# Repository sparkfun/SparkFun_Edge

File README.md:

SparkFun Edge 2
========================================

[*SparkFun Edge 2 (DEV-15420)*](https://www.sparkfun.com/products/15420)

Edge computing is here! You've probably heard of this latest entry to the long lineage of tech buzzwords like "IoT," "LoRa," and "cloud" before it, but what is “the edge” and why does it matter? The cloud is impressively powerful but all-the-time connection requires power and connectivity that may not be available. Edge computing handles discrete tasks such as determining if someone said "yes" and responds accordingly. The audio analysis is done at the edge rather than on the web. This dramatically reduces costs and complexity while limiting potential data privacy leaks.

In collaboration with Google and Ambiq, SparkFun's Edge 2 Development Board is based around the newest edge technology and is perfect for getting your feet wet with voice and even gesture recognition without relying on the distant services of other companies. The truly special feature is in the utilization of SparkFun's open-source and FCC Certified Artemis module, whose ultra-efficient ARM Cortex-M4F 48MHz (with 96MHz burst mode) processor, is spec’d to run TensorFlow Lite using only 6uA/MHz. The SparkFun Edge 2 board currently measures ~1.6mA@3V and 48MHz and can run solely on a CR2032 coin cell battery for up to 10 days. Artemis sports all the cutting edge features expected of modern microcontrollers including six configurable I2C/SPI masters, two UARTs, one I2C/SPI slave, a 15-channel 14-bit ADC, and a dedicated Bluetooth processor that supports BLE5. On top of all that the Artemis has 1MB of flash and 384KB of SRAM memory - plenty for the vast majority of applications.

On the Edge 2 you'll have built-in access to sensors, Bluetooth, I2C expansion, and GPIO inputs/outputs. To support edge computing cases like voice recognition the Edge 2 board features two MEMS microphones, an ST LIS2DH12 3-axis accelerometer on its own I2C bus, and a connector to interface to an OV7670 camera (sold separately & functionality coming soon). As TensorFlow updates their algorithms more and more features will open up for the SparkFun Edge 2. An onboard Bluetooth antenna gives the Edge 2 out-of-the-box connectivity. Also available on the board is a Qwiic connector to add I2C sensors/devices, four LEDs, and four GPIO pins. To boast the low-power capabilities of the board we've outfitted it with battery operation from the CR2032 coin cell holder. Programming the board is taken care of with an external USB-serial adapter like the Serial Basic Breakout via a serial bootloader, but for more advanced users we've also made available the JTAG programming and debugger port.

As a brave explorer of this new technology, you'll have to use some advanced concepts but don't worry. Between Ambiq Micro's Software Development Kit and our SDK Setup Guide you'll have access to plenty of examples to begin working with your hardware.

Now get out there and make something amazing with the latest machine learning technology at your very own fingertips!

Repository Contents
-------------------

* **/Documentation** - Data sheets, additional product information
* **/Firmware** - Arduino test firmware sketch
* **/Hardware** - Eagle design files (.brd, .sch)
* **/Production** - Production panel files (.brd)

Documentation
--------------
* **[Board Support Package (BSP)](https://github.com/sparkfun/SparkFun_Edge_BSP)** - Ambiq SDK Board Support Package for the SparkFun Edge.
* **[Edge Board Hookup Guide](https://learn.sparkfun.com/tutorials/sparkfun-edge-hookup-guide)** - Basic hookup guide for the SparkFun Edge.
* **[Software Development Kit (SDK) Setup Guide](https://learn.sparkfun.com/tutorials/using-sparkfun-edge-board-with-ambiq-apollo3-sdk)** - Software Development Kit for working with the SparkFun Edge.

Product Versions
----------------
* [DEV-15420](https://www.sparkfun.com/products/15420)- SparkFun Edge 2 w/ Artemis Module
* [DEV-15170](https://www.sparkfun.com/products/15170)- SparkFun Edge

Version History
---------------
* [v20](https://github.com/sparkfun/SparkFun_Edge/tree/v2.0.0) - Edge with the Artemis
* [v10](https://github.com/sparkfun/SparkFun_Edge/tree/v10) - Initial HW release

License Information
-------------------

This product is _**open source**_! 

Please review the LICENSE.md file for license information. 

If you have any questions or concerns on licensing, please contact techsupport@sparkfun.com.

Distributed as-is; no warranty is given.

- Your friends at SparkFun.

_<COLLABORATION CREDIT>_

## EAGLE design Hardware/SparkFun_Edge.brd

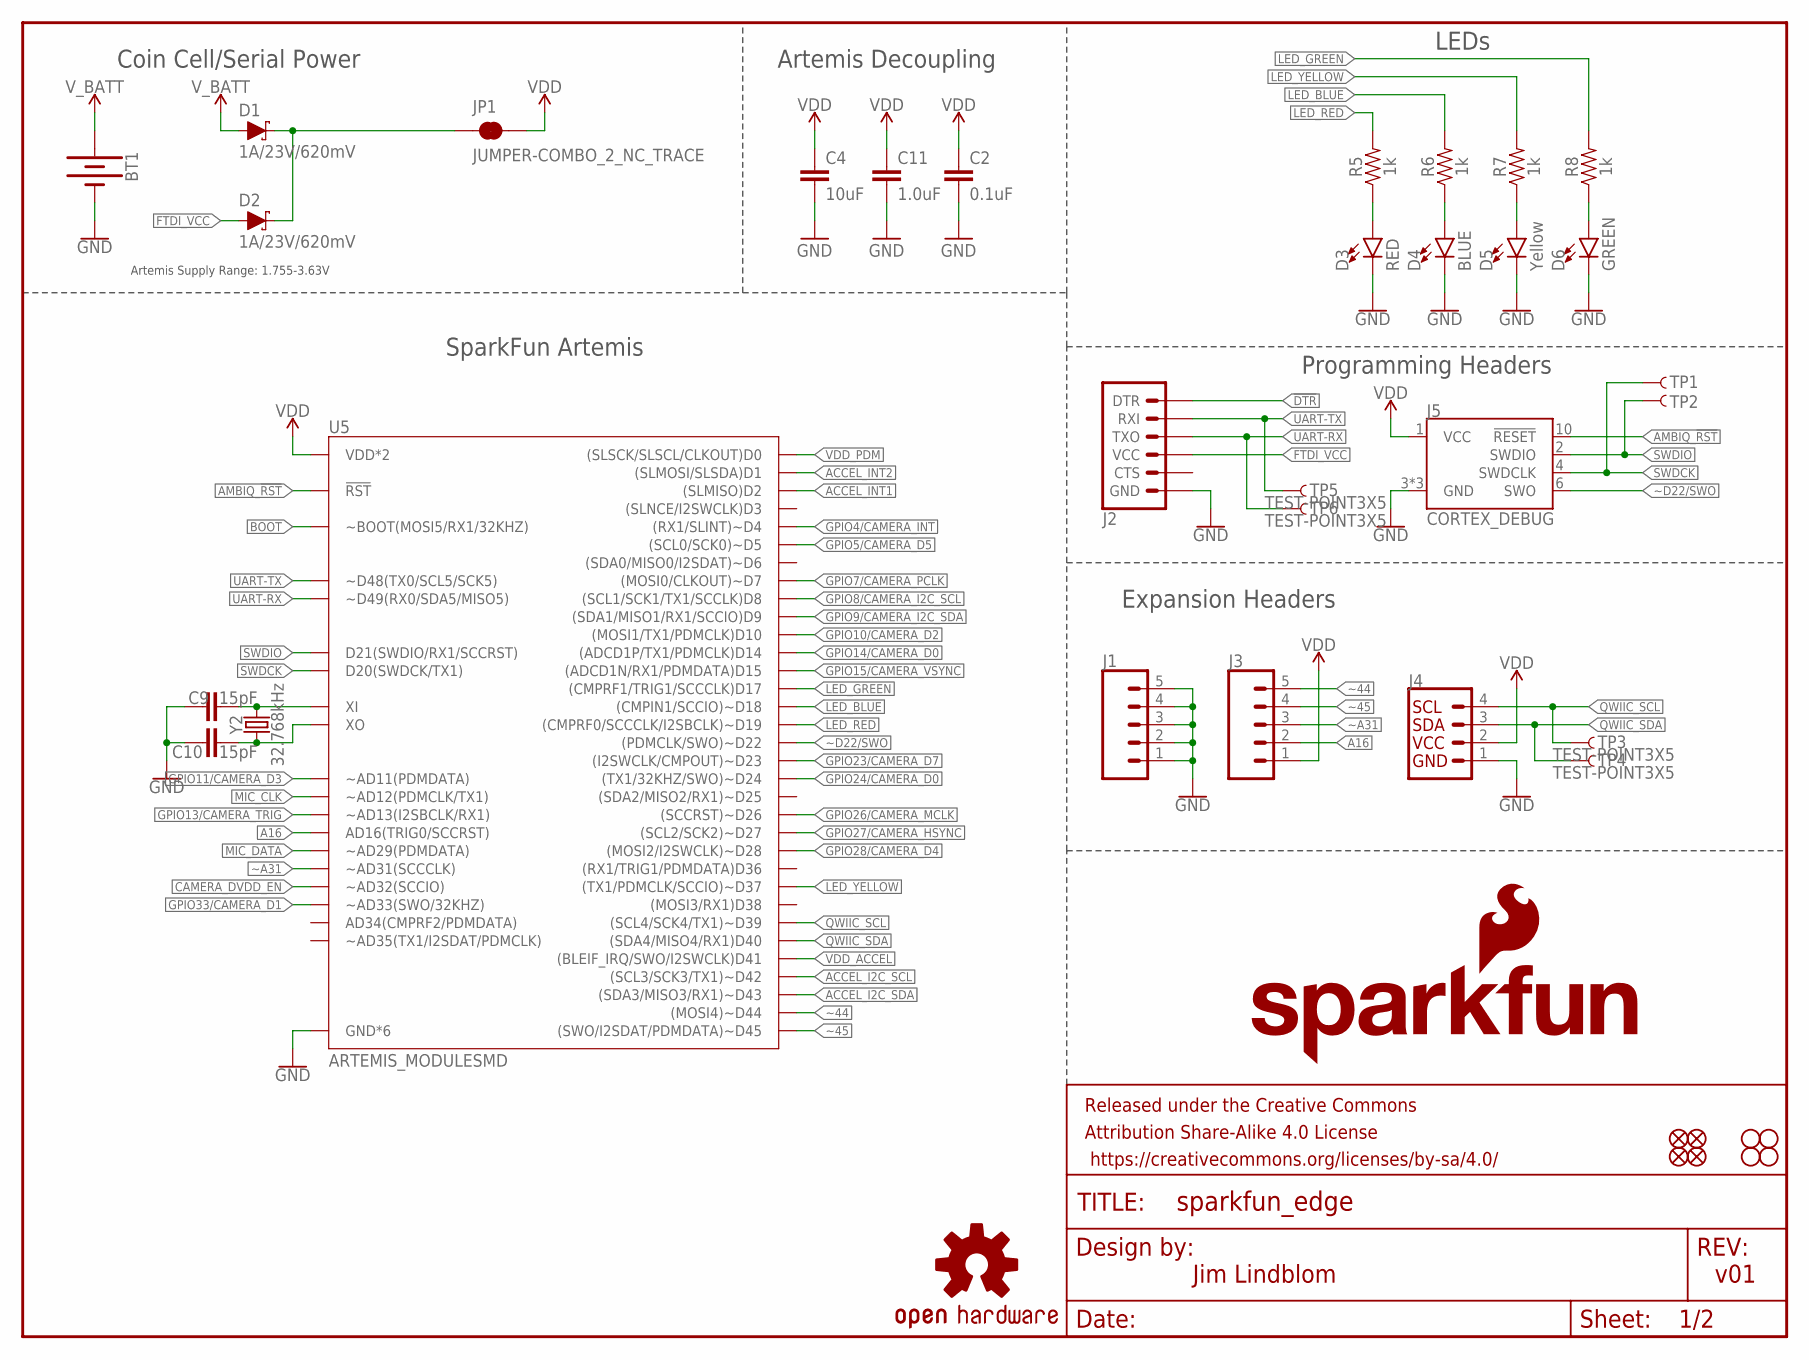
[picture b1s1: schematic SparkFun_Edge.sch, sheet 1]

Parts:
BT1: BATTERY-20MM_SMD_4LEGS_OVERPASTE_INNER; BATTCON_20MM_4LEGS_OVERPASTE_INNER
C2: 0.1uF; 0402-TIGHT
C4: 10uF; 0603
C9, C10: 15pF; 0402-TIGHT
C11: 1.0uF; 0402-TIGHT
D1, D2: 1A/23V/620mV; SOD-323
D3: RED; LED-0603
D4: BLUE; LED-0603
D5: Yellow; LED-0603
D6: GREEN; LED-0603
FD1, FD2, FD3, FD4: FIDUCIAL1X2; FIDUCIAL-1X2
FRAME1: FRAME-LETTER; CREATIVE_COMMONS
H1, H2, H3, H4: STAND-OFF
J1, J3: CONN_05NO_SILK; 1X05_NO_SILK
J2: 6_PIN_SERIAL_TARGETSMD; 1X06-SMD_RA_MALE
J4: QWIIC_CONNECTORJS-1MM; JST04_1MM_RA
J5: CORTEX_DEBUG; 2X5-PTH-1.27MM
JP1: JUMPER-COMBO_2_NC_TRACE; COMBO-JUMPER_2_NC_TRACE
LOGO1: SFE_LOGO_NAME_FLAME.1_INCH; SFE_LOGO_NAME_FLAME_.1
LOGO2: OSHW-LOGOS; OSHW-LOGO-S
R5, R6, R7, R8: 1k; 0603
TP1, TP2, TP3, TP4, TP5, TP6: TEST-POINT3X5; PAD.03X.05
U5: ARTEMIS_MODULESMD; ARTEMIS_FP
Y2: 32.768kHz; CRYSTAL-SMD-3.2X1.5MM

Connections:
!DTR: J2.1 (DTR); also elsewhere on the board
A16: J3.2, U5.AD16 (AD16(TRIG0/SCCRST))
ACCEL_I2C_SCL: U5.~D42 ((SCL3/SCK3/TX1)~D42); also elsewhere on the board
ACCEL_I2C_SDA: U5.~D43 ((SDA3/MISO3/RX1)~D43); also elsewhere on the board
ACCEL_INT1: U5.D2 ((SLMISO)D2); also elsewhere on the board
ACCEL_INT2: U5.D1 ((SLMOSI/SLSDA)D1); also elsewhere on the board
AMBIQ_!RST: J5.10 (!RESET), U5.~RST (!RST); also elsewhere on the board
BOOT: U5.BOOT (~BOOT(MOSI5/RX1/32KHZ)); also elsewhere on the board
CAMERA_DVDD_EN: U5.~AD32 (~AD32(SCCIO)); also elsewhere on the board
FTDI_VCC: D2.A, J2.4 (VCC)
GND: BT1.2 (-), C2.1, C4.2, C9.1, C10.1, C11.2, D3.C, D4.C, D5.C, D6.C, J1.1, J1.2, J1.3, J1.4, J1.5, J2.6 (GND), J4.1, J5.3 (GND), J5.5 (GND), J5.9 (GND), U5.GND@1 (GND*6), U5.GND@22 (GND*6), U5.GND@38 (GND*6), U5.GND@39 (GND*6), U5.GND@47 (GND*6), U5.GND@59 (GND*6); also elsewhere on the board
GPIO4/CAMERA_INT: U5.~D4 ((RX1/SLINT)~D4); also elsewhere on the board
GPIO5/CAMERA_D5: U5.~D5 ((SCL0/SCK0)~D5); also elsewhere on the board
GPIO7/CAMERA_PCLK: U5.D7 ((MOSI0/CLKOUT)~D7); also elsewhere on the board
GPIO8/CAMERA_I2C_SCL: U5.D8 ((SCL1/SCK1/TX1/SCCLK)D8); also elsewhere on the board
GPIO9/CAMERA_I2C_SDA: U5.D9 ((SDA1/MISO1/RX1/SCCIO)D9); also elsewhere on the board
GPIO10/CAMERA_D2: U5.D10 ((MOSI1/TX1/PDMCLK)D10); also elsewhere on the board
GPIO11/CAMERA_D3: U5.~AD11 (~AD11(PDMDATA)); also elsewhere on the board
GPIO13/CAMERA_TRIG: U5.~AD13 (~AD13(I2SBCLK/RX1)); also elsewhere on the board
GPIO14/CAMERA_D0: U5.D14 ((ADCD1P/TX1/PDMCLK)D14); also elsewhere on the board
GPIO15/CAMERA_VSYNC: U5.D15 ((ADCD1N/RX1/PDMDATA)D15); also elsewhere on the board
GPIO23/CAMERA_D7: U5.~D23 ((I2SWCLK/CMPOUT)~D23); also elsewhere on the board
GPIO24/CAMERA_D0: U5.~D24 ((TX1/32KHZ/SWO)~D24); also elsewhere on the board
GPIO26/CAMERA_MCLK: U5.~D26 ((SCCRST)~D26); also elsewhere on the board
GPIO27/CAMERA_HSYNC: U5.~D27 ((SCL2/SCK2)~D27); also elsewhere on the board
GPIO28/CAMERA_D4: U5.~D28 ((MOSI2/I2SWCLK)~D28); also elsewhere on the board
GPIO33/CAMERA_D1: U5.~AD33/SWO (~AD33(SWO/32KHZ)); also elsewhere on the board
LED_BLUE: R6.2, U5.~D18 ((CMPIN1/SCCIO)~D18)
LED_GREEN: R8.2, U5.D17 ((CMPRF1/TRIG1/SCCCLK)D17)
LED_RED: R5.2, U5.~D19 ((CMPRF0/SCCCLK/I2SBCLK)~D19)
LED_YELLOW: R7.2, U5.~D37 ((TX1/PDMCLK/SCCIO)~D37)
MIC_CLK: U5.~AD12 (~AD12(PDMCLK/TX1)); also elsewhere on the board
MIC_DATA: U5.~AD29 (~AD29(PDMDATA)); also elsewhere on the board
unnamed: C9.2, U5.XI, Y2.P$2 (2)
unnamed: D4.A, R6.1
unnamed: D3.A, R5.1
unnamed: D5.A, R7.1
unnamed: D6.A, R8.1
QWIIC_SCL: J4.4, TP3.P$1, U5.~D39 ((SCL4/SCK4/TX1)~D39)
QWIIC_SDA: J4.3, TP4.P$1, U5.D40 ((SDA4/MISO4/RX1)D40)
SWDCK: J5.4 (SWDCLK), TP1.P$1, U5.SWDCK (D20(SWDCK/TX1))
SWDIO: J5.2 (SWDIO), TP2.P$1, U5.SWDIO (D21(SWDIO/RX1/SCCRST))
UART-RX: J2.3 (TXO), TP6.P$1, U5.RXI-0 (~D49(RX0/SDA5/MISO5))
UART-TX: J2.2 (RXI), TP5.P$1, U5.TXO-0 (~D48(TX0/SCL5/SCK5))
VDD: C2.2, C4.1, C11.1, J3.1, J4.2, J5.1 (VCC), JP1.2, JP1.4 (2), U5.VDD@36 (VDD*2), U5.VDD@37 (VDD*2); also elsewhere on the board
VDD_ACCEL: U5.D41 ((BLEIF_IRQ/SWO/I2SWCLK)D41); also elsewhere on the board
VDD_PDM: U5.D0 ((SLSCK/SLSCL/CLKOUT)D0); also elsewhere on the board
VIN1: D1.C, D2.C, JP1.1, JP1.3 (1)
V_BATT: BT1.1 (+), D1.A
X0: C10.2, U5.XO, Y2.P$1 (1)
~44: J3.5, U5.~D44 ((MOSI4)~D44)
~45: J3.4, U5.~D45 ((SWO/I2SDAT/PDMDATA)~D45)
~A31: J3.3, U5.~AD31 (~AD31(SCCCLK))
~D22/SWO: J5.6 (SWO), U5.~D22 ((PDMCLK/SWO)~D22)

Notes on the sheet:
v01
Jim Lindblom
Artemis Supply Range: 1.755-3.63V
SparkFun Artemis
Coin Cell/Serial Power
Artemis Decoupling
LEDs
Programming Headers
Expansion Headers

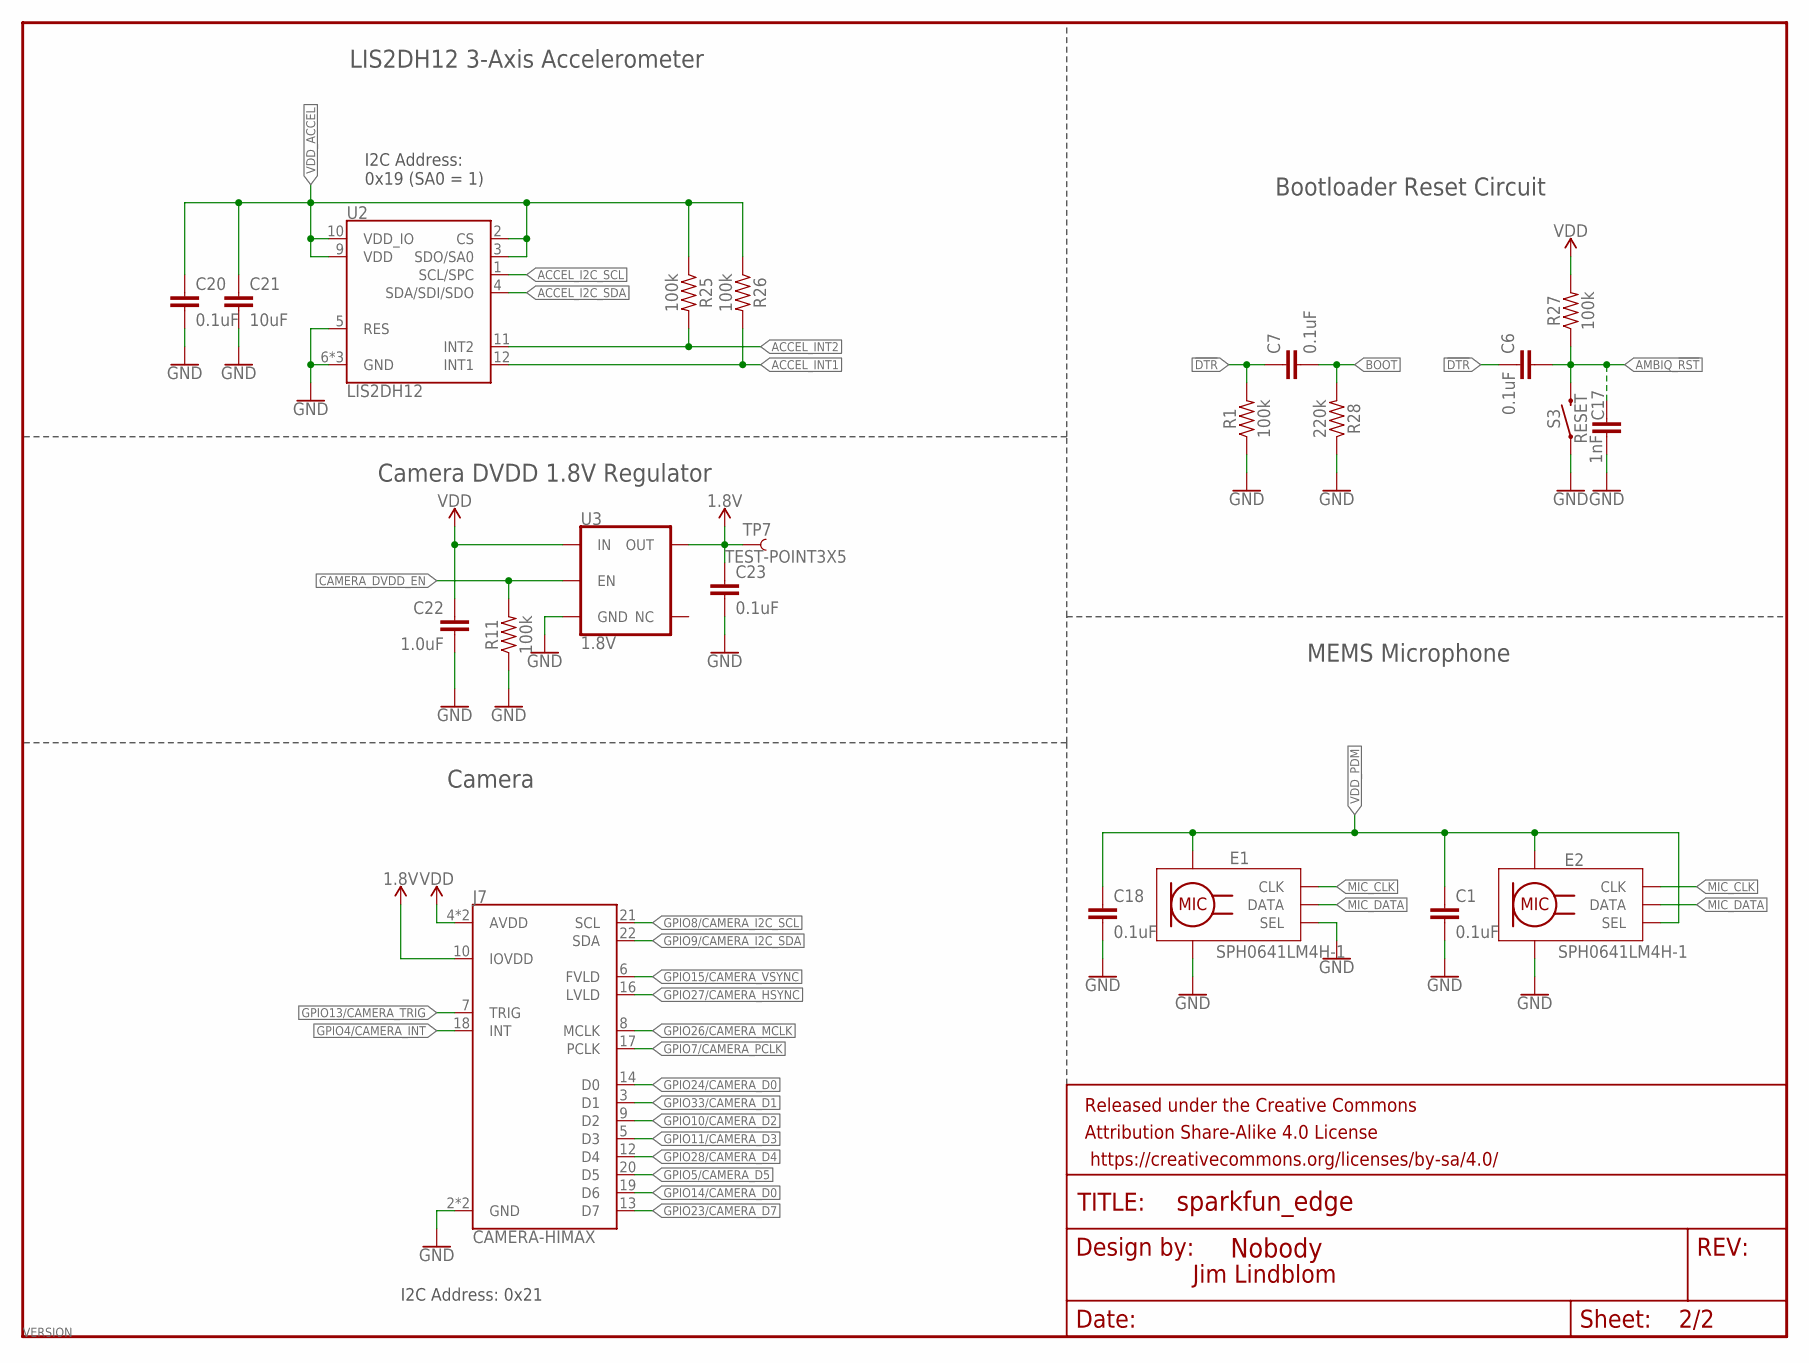
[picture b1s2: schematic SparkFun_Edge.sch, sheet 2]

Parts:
C1, C18, C20, C23: 0.1uF; 0402-TIGHT
C6, C7: 0.1uF; 0603
C17: 1nF; 0603
C21: 10uF; 0603
C22: 1.0uF; 0402-TIGHT
E1, E2: SPH0641LM4H-1; SPH0641LM4H-1_MICROPHONE
FRAME2: FRAME-LETTERNO_PACKAGE; DUMMY
J7: CAMERA-HIMAX; FPC-24-AMPHENOL-SFV24R-1STE1HLF
R1, R27: 100k; 0603
R11, R25, R26: 100k; 0402-TIGHT
R28: 220k; 0603
S3: RESET; TACTILE_SWITCH_SMD_4.6X2.8MM
TP7: TEST-POINT3X5; PAD.03X.05
U2: LIS2DH12; LGA-12-LISDH12
U3: 1.8V; SOT23-5

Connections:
1.8V: C23.1, J7.10 (IOVDD), TP7.P$1, U3.5 (OUT)
!DTR: C6.1, C7.1, R1.2; also elsewhere on the board
ACCEL_I2C_SCL: U2.1 (SCL/SPC); also elsewhere on the board
ACCEL_I2C_SDA: U2.4 (SDA/SDI/SDO); also elsewhere on the board
ACCEL_INT1: R26.2, U2.12 (INT1); also elsewhere on the board
ACCEL_INT2: R25.2, U2.11 (INT2); also elsewhere on the board
AMBIQ_!RST: C6.2, C17.1, R27.1, S3.3 (2), S3.4 (2); also elsewhere on the board
BOOT: C7.2, R28.2; also elsewhere on the board
CAMERA_DVDD_EN: R11.2, U3.3 (EN); also elsewhere on the board
GND: C1.2, C17.2, C18.2, C20.2, C21.2, C22.2, C23.2, E1.2 (SEL), E1.3 (GND), E1.6 (GND), E1.7 (GND), E1.8 (GND), E2.3 (GND), E2.6 (GND), E2.7 (GND), E2.8 (GND), J7.2 (GND), J7.15 (GND), R1.1, R11.1, R28.1, S3.1, S3.2 (1), U2.5 (RES), U2.6 (GND), U2.7 (GND), U2.8 (GND), U3.2 (GND); also elsewhere on the board
GPIO4/CAMERA_INT: J7.18 (INT); also elsewhere on the board
GPIO5/CAMERA_D5: J7.20 (D5); also elsewhere on the board
GPIO7/CAMERA_PCLK: J7.17 (PCLK); also elsewhere on the board
GPIO8/CAMERA_I2C_SCL: J7.21 (SCL); also elsewhere on the board
GPIO9/CAMERA_I2C_SDA: J7.22 (SDA); also elsewhere on the board
GPIO10/CAMERA_D2: J7.9 (D2); also elsewhere on the board
GPIO11/CAMERA_D3: J7.5 (D3); also elsewhere on the board
GPIO13/CAMERA_TRIG: J7.7 (TRIG); also elsewhere on the board
GPIO14/CAMERA_D0: J7.19 (D6); also elsewhere on the board
GPIO15/CAMERA_VSYNC: J7.6 (FVLD); also elsewhere on the board
GPIO23/CAMERA_D7: J7.13 (D7); also elsewhere on the board
GPIO24/CAMERA_D0: J7.14 (D0); also elsewhere on the board
GPIO26/CAMERA_MCLK: J7.8 (MCLK); also elsewhere on the board
GPIO27/CAMERA_HSYNC: J7.16 (LVLD); also elsewhere on the board
GPIO28/CAMERA_D4: J7.12 (D4); also elsewhere on the board
GPIO33/CAMERA_D1: J7.3 (D1); also elsewhere on the board
MIC_CLK: E1.4 (CLK), E2.4 (CLK); also elsewhere on the board
MIC_DATA: E1.1 (DATA), E2.1 (DATA); also elsewhere on the board
VDD: C22.1, J7.4 (AVDD), J7.11 (AVDD), R27.2, U3.1 (IN); also elsewhere on the board
VDD_ACCEL: C20.1, C21.1, R25.1, R26.1, U2.2 (CS), U2.3 (SDO/SA0), U2.9 (VDD), U2.10 (VDD_IO); also elsewhere on the board
VDD_PDM: C1.1, C18.1, E1.5 (VDD), E2.2 (SEL), E2.5 (VDD); also elsewhere on the board

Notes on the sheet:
Camera DVDD 1.8V Regulator
LIS2DH12 3-Axis Accelerometer
Jim Lindblom
I2C Address: 0x19 (SA0 = 1)
I2C Address: 0x21
Camera
MEMS Microphone
Bootloader Reset Circuit

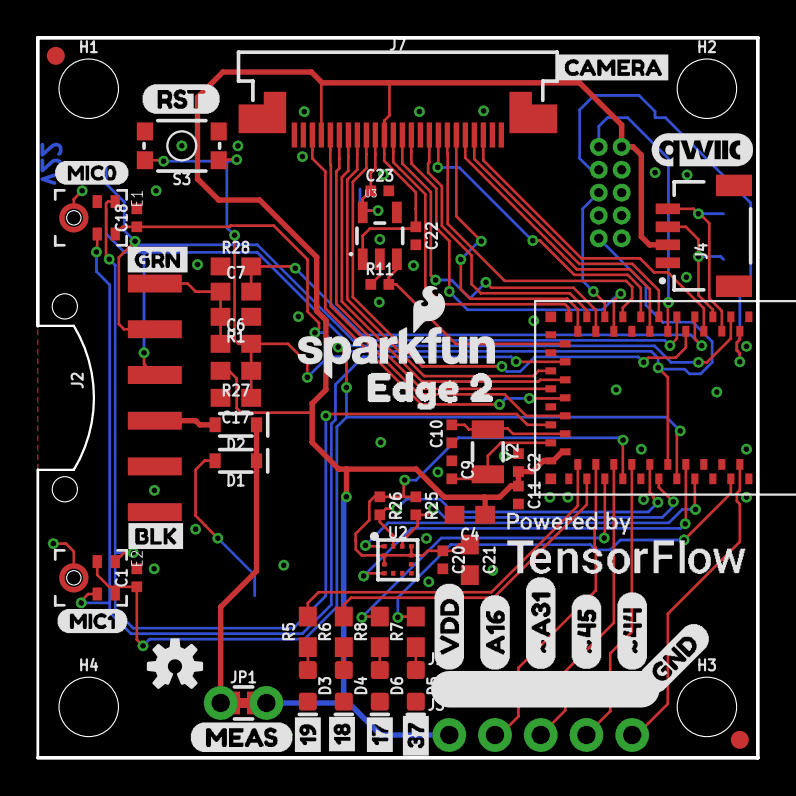
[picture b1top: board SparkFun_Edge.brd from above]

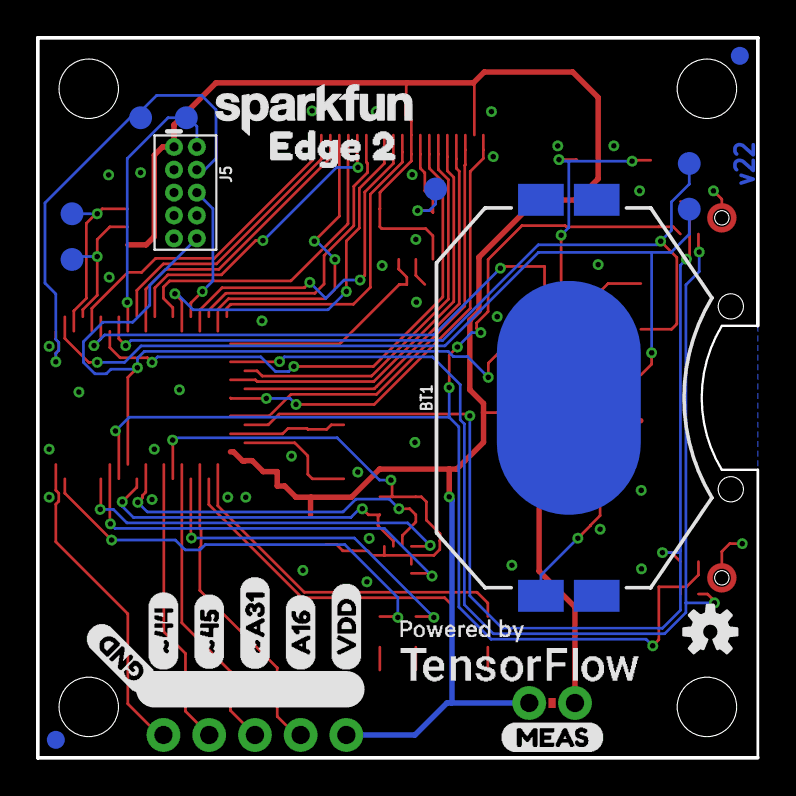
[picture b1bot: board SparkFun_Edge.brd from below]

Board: 2 copper layers, 40.0 x 40.0 mm, 95 parts (22 on the bottom side), 55 nets.

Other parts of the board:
U$1: MIC00
U$2: BLK2
U$3, U$14: GND0
U$4, U$9: VDD1
U$5, U$12: #453
U$6, U$11: #A312
U$7, U$10: A161
U$8: MIC10
U$13, U$36: #444
U$15, U$32: EDGE_20
U$16: 372
U$19: QWIIC_COPYRIGHT_SMALL
U$20: CAMERA3
U$21, U$25: POWEREDBY_TF#JPG
U$23: 171
U$24, U$35: MEAS10
U$26: 182
U$27: RST15
U$28: GRN1
U$29: SFE_LOGO_NAME_.1
U$30: OSHW-LOGO-S
U$31: 193

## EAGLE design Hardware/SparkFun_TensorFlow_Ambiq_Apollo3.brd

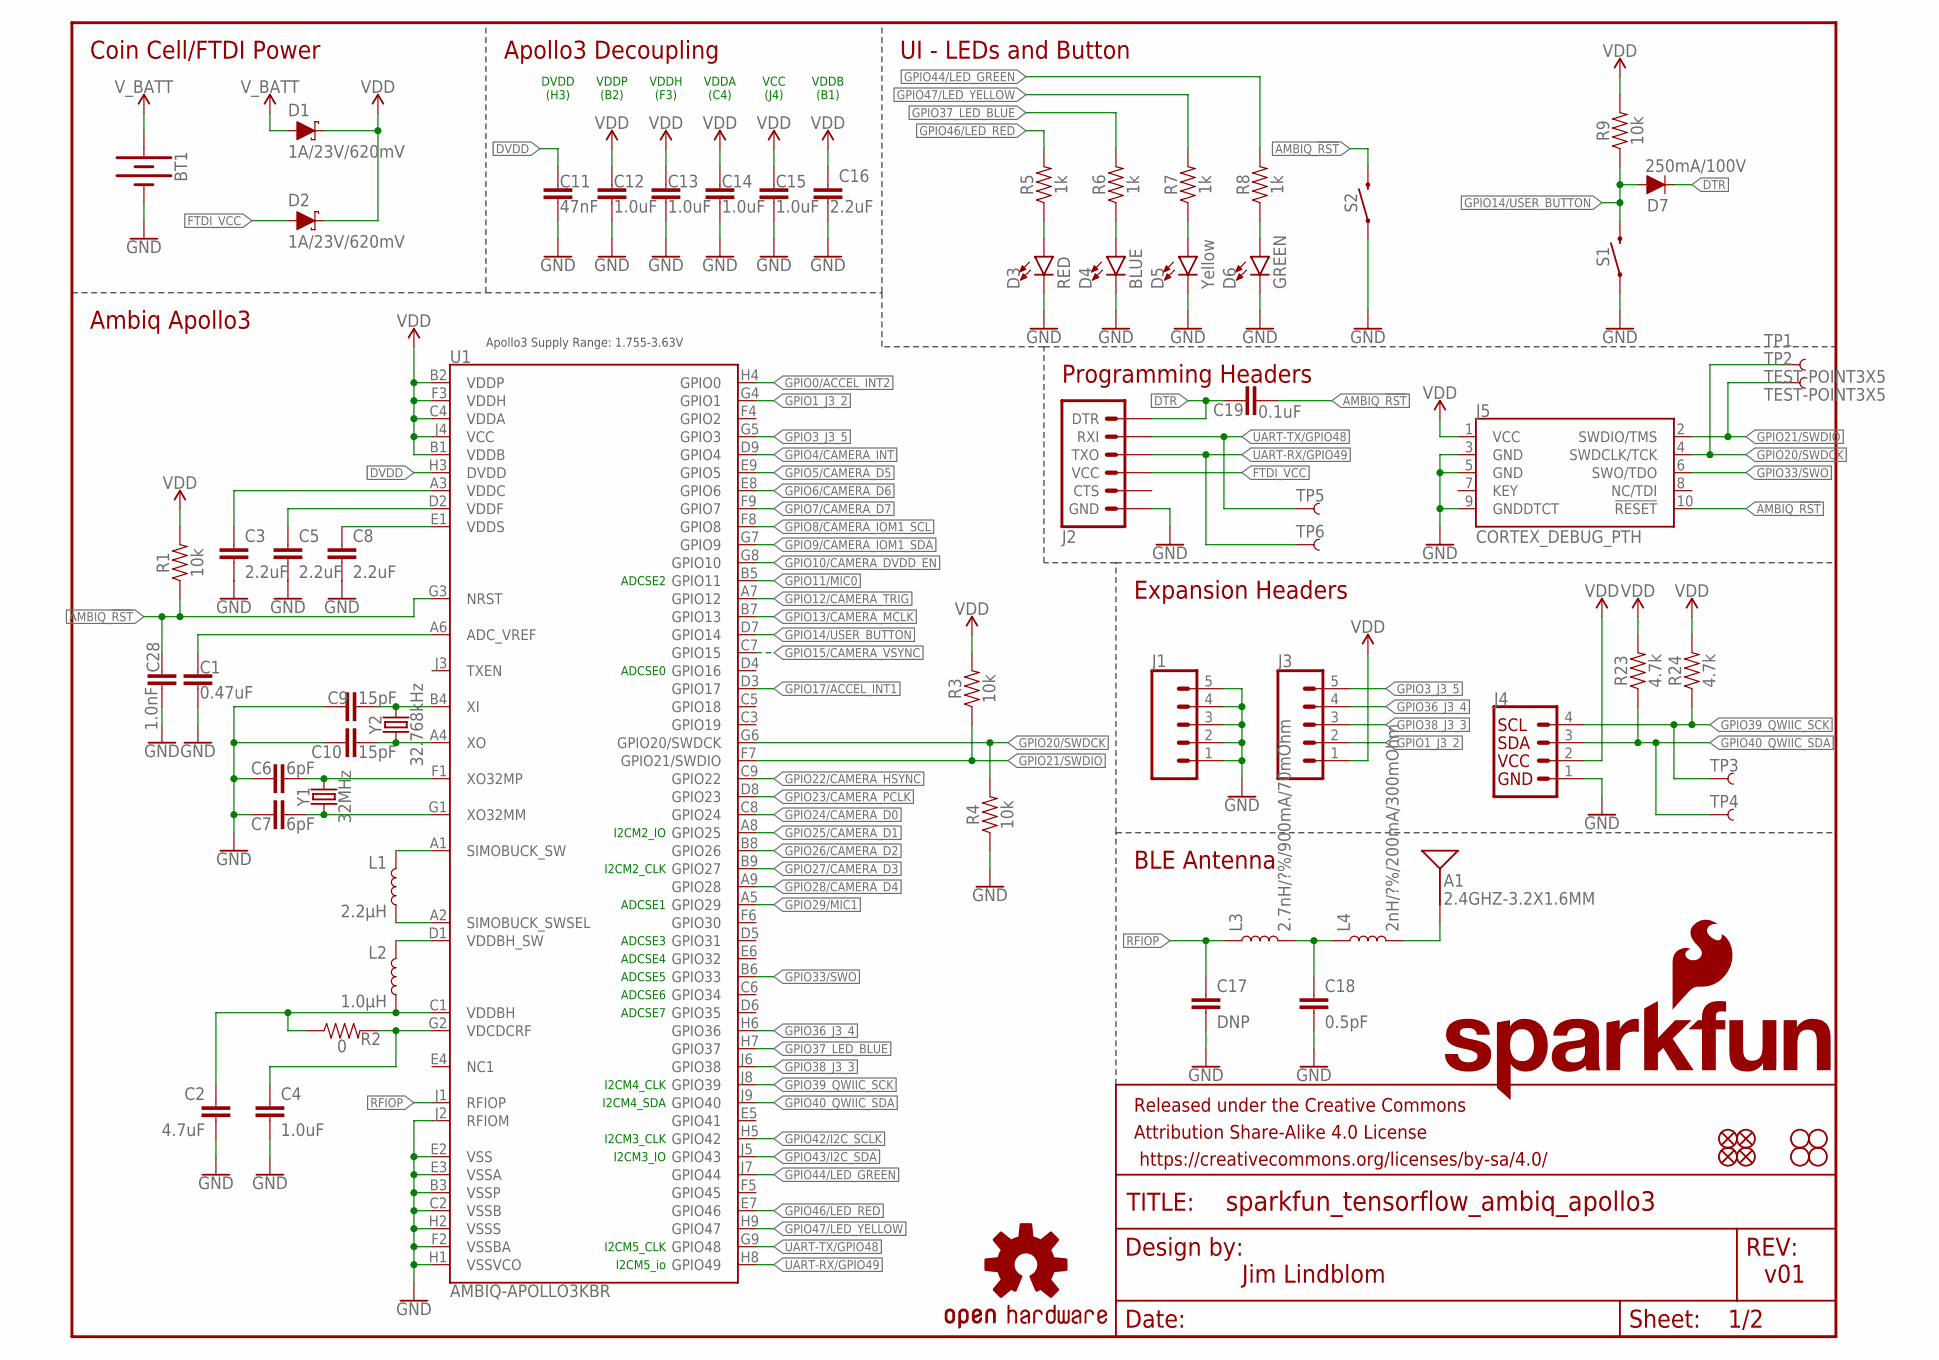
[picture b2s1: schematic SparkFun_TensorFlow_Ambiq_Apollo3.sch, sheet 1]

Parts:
A1: 2.4GHZ-3.2X1.6MM; ANT-2.4GHZ-3.2X1.6X1.2MM
BT1: BATTERY-20MM_SMD_4LEGS_OVERPASTE_INNER; BATTCON_20MM_4LEGS_OVERPASTE_INNER
C1: 0.47uF; 0402-TIGHT
C2: 4.7uF; 0402-TIGHT
C3, C5, C8, C16: 2.2uF; 0402-TIGHT
C4, C12, C13, C14, C15: 1.0uF; 0402-TIGHT
C6, C7: 6pF; 0402-TIGHT
C9, C10: 15pF; 0402-TIGHT
C11: 47nF; 0402-TIGHT
C17: DNP; 0402-TIGHT
C18: 0.5pF; 0402-TIGHT
C19: 0.1uF; 0402-TIGHT
C28: 1.0nF; 0402-TIGHT
D1, D2: 1A/23V/620mV; SOD-323@1
D3: RED; LED-0603
D4: BLUE; LED-0603
D5: Yellow; LED-0603
D6: GREEN; LED-0603
D7: 250mA/100V; SOD-323
FD1, FD2, FD3, FD4: FIDUCIAL1X2; FIDUCIAL-1X2
FRAME1: FRAME-LETTER; CREATIVE_COMMONS
H1, H2, H3, H4: STAND-OFF
J1, J3: CONN_05NO_SILK; 1X05_NO_SILK
J2: 6_PIN_SERIAL_TARGETSMD; 1X06-SMD_RA_MALE
J4: QWIIC_CONNECTORJS-1MM; 1X04_1MM_RA
J5: CORTEX_DEBUG_PTH; 2X5-PTH-1.27MM
L1: 2.2μH; 0805-WIDE
L2: 1.0μH; 0805-WIDE
L3: 2.7nH/?%/900mA/70mOhm; 0402-TIGHT
L4: 2nH/?%/200mA/300mOhm; 0402-TIGHT
LOGO1: SFE_LOGO_NAME_FLAME.1_INCH; SFE_LOGO_NAME_FLAME_.1
LOGO2: OSHW-LOGOS; OSHW-LOGO-S
R1, R3, R4, R9: 10k; 0402
R2: 0; 0402
R5, R6, R7, R8: 1k; 0603
R23, R24: 4.7k; 0603
S1, S2: MOMENTARY-SWITCH-SPST-SMD-5.2-TALL-REDUNDANT; TACTILE_SWITCH_SMD_5.2MM
TP1, TP2, TP3, TP4, TP5, TP6: TEST-POINT3X5; PAD.03X.05
U1: AMBIQ-APOLLO3KBR; BGA-81-5X5MM
Y1: 32MHz; CRYSTAL-SMD-2.0X1.6MM
Y2: 32.768kHz; CRYSTAL-SMD-3.2X1.5MM

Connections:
ADC_VREF: C1.1, U1.A6 (ADC_VREF)
AMBIQ_!RST: C19.2, C28.1, J5.10 (!RESET), R1.1, S2.3 (2), S2.4 (2), U1.G3 (NRST)
DTR: C19.1, D7.C, J2.1 (DTR)
DVDD: C11.1, U1.H3 (DVDD)
FTDI_VCC: D2.A, J2.4 (VCC)
GND: BT1.2 (-), C1.2, C2.2, C3.2, C4.2, C5.2, C6.1, C7.1, C8.2, C9.1, C10.1, C11.2, C12.2, C13.2, C14.2, C15.2, C16.2, C17.2, C18.2, C28.2, D3.C, D4.C, D5.C, D6.C, J1.1, J1.2, J1.3, J1.4, J1.5, J2.6 (GND), J4.1, J5.3 (GND), J5.5 (GND), J5.9 (GNDDTCT), R4.1, S1.1, S1.2 (1), S2.1, S2.2 (1), U1.B3 (VSSP), U1.C2 (VSSB), U1.E2 (VSS), U1.E3 (VSSA), U1.F2 (VSSBA), U1.H1 (VSSVCO), U1.H2 (VSSS), U1.J2 (RFIOM); also elsewhere on the board
GPIO0/ACCEL_INT2: U1.H4 (GPIO0); also elsewhere on the board
GPIO1_J3_2: J3.2, U1.G4 (GPIO1)
GPIO3_J3_5: J3.5, U1.G5 (GPIO3)
GPIO4/CAMERA_INT: U1.D9 (GPIO4); also elsewhere on the board
GPIO5/CAMERA_D5: U1.E9 (GPIO5); also elsewhere on the board
GPIO6/CAMERA_D6: U1.E8 (GPIO6); also elsewhere on the board
GPIO7/CAMERA_D7: U1.F9 (GPIO7); also elsewhere on the board
GPIO8/CAMERA_IOM1_SCL: U1.F8 (GPIO8); also elsewhere on the board
GPIO9/CAMERA_IOM1_SDA: U1.G7 (GPIO9); also elsewhere on the board
GPIO10/CAMERA_DVDD_EN: U1.G8 (GPIO10); also elsewhere on the board
GPIO11/MIC0: U1.B5 (GPIO11); also elsewhere on the board
GPIO12/CAMERA_TRIG: U1.A7 (GPIO12); also elsewhere on the board
GPIO13/CAMERA_MCLK: U1.B7 (GPIO13); also elsewhere on the board
GPIO14/USER_BUTTON: D7.A, R9.1, S1.3 (2), S1.4 (2), U1.D7 (GPIO14)
GPIO15/CAMERA_VSYNC: U1.C7 (GPIO15); also elsewhere on the board
GPIO17/ACCEL_INT1: U1.D3 (GPIO17); also elsewhere on the board
GPIO20/SWDCK: J5.4 (SWDCLK/TCK), R4.2, TP1.P$1, U1.G6 (GPIO20/SWDCK)
GPIO21/SWDIO: J5.2 (SWDIO/TMS), R3.1, TP2.P$1, U1.F7 (GPIO21/SWDIO)
GPIO22/CAMERA_HSYNC: U1.C9 (GPIO22); also elsewhere on the board
GPIO23/CAMERA_PCLK: U1.D8 (GPIO23); also elsewhere on the board
GPIO24/CAMERA_D0: U1.C8 (GPIO24); also elsewhere on the board
GPIO25/CAMERA_D1: U1.A8 (GPIO25); also elsewhere on the board
GPIO26/CAMERA_D2: U1.B8 (GPIO26); also elsewhere on the board
GPIO27/CAMERA_D3: U1.B9 (GPIO27); also elsewhere on the board
GPIO28/CAMERA_D4: U1.A9 (GPIO28); also elsewhere on the board
GPIO29/MIC1: U1.A5 (GPIO29); also elsewhere on the board
GPIO33/SWO: J5.6 (SWO/TDO), U1.B6 (GPIO33)
GPIO36_J3_4: J3.4, U1.H6 (GPIO36)
GPIO37_LED_BLUE: R6.2, U1.H7 (GPIO37)
GPIO38_J3_3: J3.3, U1.J6 (GPIO38)
GPIO39_QWIIC_SCK: J4.4, R24.1, TP3.P$1, U1.J8 (GPIO39)
GPIO40_QWIIC_SDA: J4.3, R23.1, TP4.P$1, U1.J9 (GPIO40)
GPIO42/I2C_SCLK: U1.H5 (GPIO42); also elsewhere on the board
GPIO43/I2C_SDA: U1.J5 (GPIO43); also elsewhere on the board
GPIO44/LED_GREEN: R8.2, U1.J7 (GPIO44)
GPIO46/LED_RED: R5.2, U1.E7 (GPIO46)
GPIO47/LED_YELLOW: R7.2, U1.H9 (GPIO47)
unnamed: A1.FEED, L4.2
unnamed: C7.2, U1.G1 (XO32MM), Y1.1
unnamed: C6.2, U1.F1 (XO32MP), Y1.3 (2)
unnamed: D4.A, R6.1
unnamed: D3.A, R5.1
unnamed: D5.A, R7.1
unnamed: D6.A, R8.1
unnamed: C18.1, L3.2, L4.1
RFIOP: C17.1, L3.1, U1.J1 (RFIOP)
SIMBUCK_SWSEL: L1.2, U1.A2 (SIMOBUCK_SWSEL)
SIMOBUCK_SW: L1.1, U1.A1 (SIMOBUCK_SW)
UART-RX/GPIO49: J2.3 (TXO), TP6.P$1, U1.H8 (GPIO49)
UART-TX/GPIO48: J2.2 (RXI), TP5.P$1, U1.G9 (GPIO48)
VDCDCRF: C4.1, R2.2, U1.G2 (VDCDCRF)
VDD: C12.1, C13.1, C14.1, C15.1, C16.1, D1.C, D2.C, J3.1, J4.2, J5.1 (VCC), R1.2, R3.2, R9.2, R23.2, R24.2, U1.B1 (VDDB), U1.B2 (VDDP), U1.C4 (VDDA), U1.F3 (VDDH), U1.J4 (VCC); also elsewhere on the board
VDDBH: C2.1, L2.2, R2.1, U1.C1 (VDDBH)
VDDBH_SW: L2.1, U1.D1 (VDDBH_SW)
VDDC: C3.1, U1.A3 (VDDC)
VDDF: C5.1, U1.D2 (VDDF)
VDDS: C8.1, U1.E1 (VDDS)
V_BATT: BT1.1 (+), D1.A
X0: C10.2, U1.A4 (XO), Y2.P$1 (1)
XI: C9.2, U1.B4 (XI), Y2.P$2 (2)

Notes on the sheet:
DVDD (H3)
VDDP (B2)
VDDH (F3)
VDDA (C4)
VCC (J4)
VDDB (B1)
ADCSE0
ADCSE1
ADCSE2
ADCSE3
I2CM2_IO
I2CM2_CLK
I2CM4_CLK
I2CM4_SDA
I2CM3_CLK
I2CM3_IO
I2CM5_CLK
I2CM5_io
ADCSE6
ADCSE4
ADCSE5
ADCSE7
v01
Jim Lindblom
Apollo3 Supply Range: 1.755-3.63V
Ambiq Apollo3
Coin Cell/FTDI Power
Apollo3 Decoupling
UI - LEDs and Button
Programming Headers
Expansion Headers
BLE Antenna

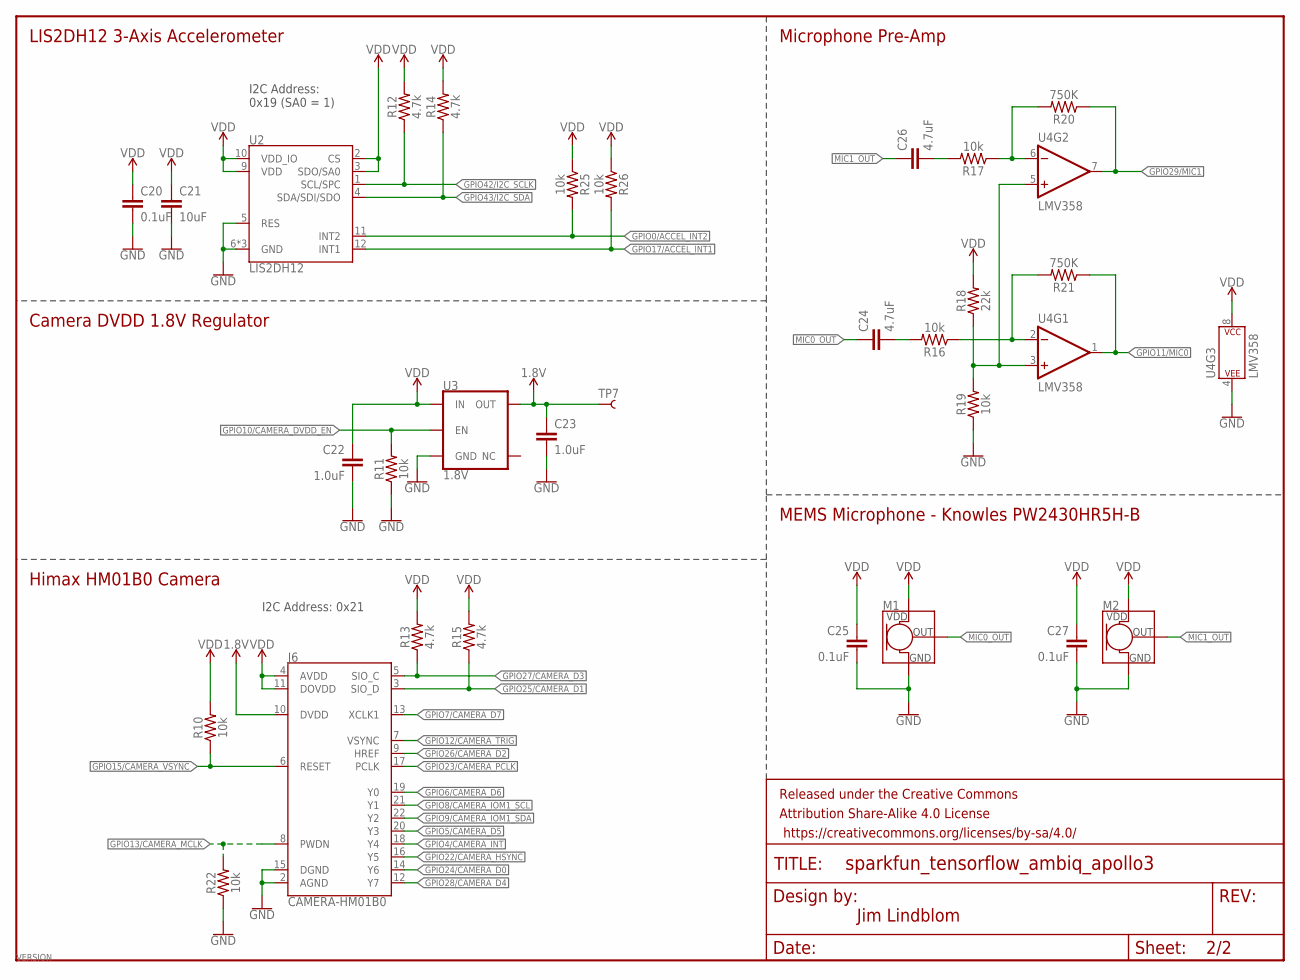
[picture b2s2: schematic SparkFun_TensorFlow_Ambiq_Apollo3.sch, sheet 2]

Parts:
C20, C25, C27: 0.1uF; 0402-TIGHT
C21: 10uF; 0603
C22, C23: 1.0uF; 0402-TIGHT
C24, C26: 4.7uF; 0603
FRAME2: FRAME-LETTERNO_PACKAGE; DUMMY
J6: CAMERA-HM01B0; FPC-24-AMPHENOL-SFV24R-1STE1HLF
M1, M2: MEMS_MIC; SPW2430HR5H-B
R10, R11, R19, R22, R25, R26: 10k; 0402
R12, R13, R14, R15: 4.7k; 0603
R16, R17: 10k; 0603
R18: 22k; 0402-TIGHT
R20, R21: 750K; 0603
TP7: TEST-POINT3X5; PAD.03X.05
U2: LIS2DH12; LGA-12-LISDH12
U3: 1.8V; SOT23-5
U4: LMV358; SO08

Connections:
1.8V: C23.1, J6.10 (DVDD), TP7.P$1, U3.5 (OUT)
GND: C20.2, C21.2, C22.2, C23.2, C25.2, C27.2, J6.2 (AGND), J6.15 (DGND), M1.2 (GND), M1.3 (GND), M2.2 (GND), M2.3 (GND), R11.1, R19.1, R22.1, U2.5 (RES), U2.6 (GND), U2.7 (GND), U2.8 (GND), U3.2 (GND), U4.4 (P$V-); also elsewhere on the board
GPIO0/ACCEL_INT2: R25.2, U2.11 (INT2); also elsewhere on the board
GPIO4/CAMERA_INT: J6.18 (Y4); also elsewhere on the board
GPIO5/CAMERA_D5: J6.20 (Y3); also elsewhere on the board
GPIO6/CAMERA_D6: J6.19 (Y0); also elsewhere on the board
GPIO7/CAMERA_D7: J6.13 (XCLK1); also elsewhere on the board
GPIO8/CAMERA_IOM1_SCL: J6.21 (Y1); also elsewhere on the board
GPIO9/CAMERA_IOM1_SDA: J6.22 (Y2); also elsewhere on the board
GPIO10/CAMERA_DVDD_EN: R11.2, U3.3 (EN); also elsewhere on the board
GPIO11/MIC0: R21.1, U4.1 (OUT); also elsewhere on the board
GPIO12/CAMERA_TRIG: J6.7 (VSYNC); also elsewhere on the board
GPIO13/CAMERA_MCLK: J6.8 (PWDN), R22.2; also elsewhere on the board
GPIO15/CAMERA_VSYNC: J6.6 (RESET), R10.1; also elsewhere on the board
GPIO17/ACCEL_INT1: R26.2, U2.12 (INT1); also elsewhere on the board
GPIO22/CAMERA_HSYNC: J6.16 (Y5); also elsewhere on the board
GPIO23/CAMERA_PCLK: J6.17 (PCLK); also elsewhere on the board
GPIO24/CAMERA_D0: J6.14 (Y6); also elsewhere on the board
GPIO25/CAMERA_D1: J6.3 (SIO_D), R15.1; also elsewhere on the board
GPIO26/CAMERA_D2: J6.9 (HREF); also elsewhere on the board
GPIO27/CAMERA_D3: J6.5 (SIO_C), R13.1; also elsewhere on the board
GPIO28/CAMERA_D4: J6.12 (Y7); also elsewhere on the board
GPIO29/MIC1: R20.1, U4.7 (OUT); also elsewhere on the board
GPIO42/I2C_SCLK: R12.1, U2.1 (SCL/SPC); also elsewhere on the board
GPIO43/I2C_SDA: R14.1, U2.4 (SDA/SDI/SDO); also elsewhere on the board
MIC0_OUT: C24.1, M1.1 (OUT)
MIC1_OUT: C26.1, M2.1 (OUT)
unnamed: R18.1, R19.2, U4.3 (+IN), U4.5 (+IN)
unnamed: C24.2, R16.2
unnamed: R17.1, R20.2, U4.6 (-IN)
unnamed: R16.1, R21.2, U4.2 (-IN)
unnamed: C26.2, R17.2
VDD: C20.1, C21.1, C22.1, C25.1, C27.1, J6.4 (AVDD), J6.11 (DOVDD), M1.4 (VDD), M2.4 (VDD), R10.2, R12.2, R13.2, R14.2, R15.2, R18.2, R25.1, R26.1, U2.2 (CS), U2.3 (SDO/SA0), U2.9 (VDD), U2.10 (VDD_IO), U3.1 (IN), U4.8 (P$V+); also elsewhere on the board

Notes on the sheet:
Camera DVDD 1.8V Regulator
LIS2DH12 3-Axis Accelerometer
Microphone Pre-Amp
Jim Lindblom
I2C Address: 0x19 (SA0 = 1)
I2C Address: 0x21
Himax HM01B0 Camera
MEMS Microphone - Knowles PW2430HR5H-B

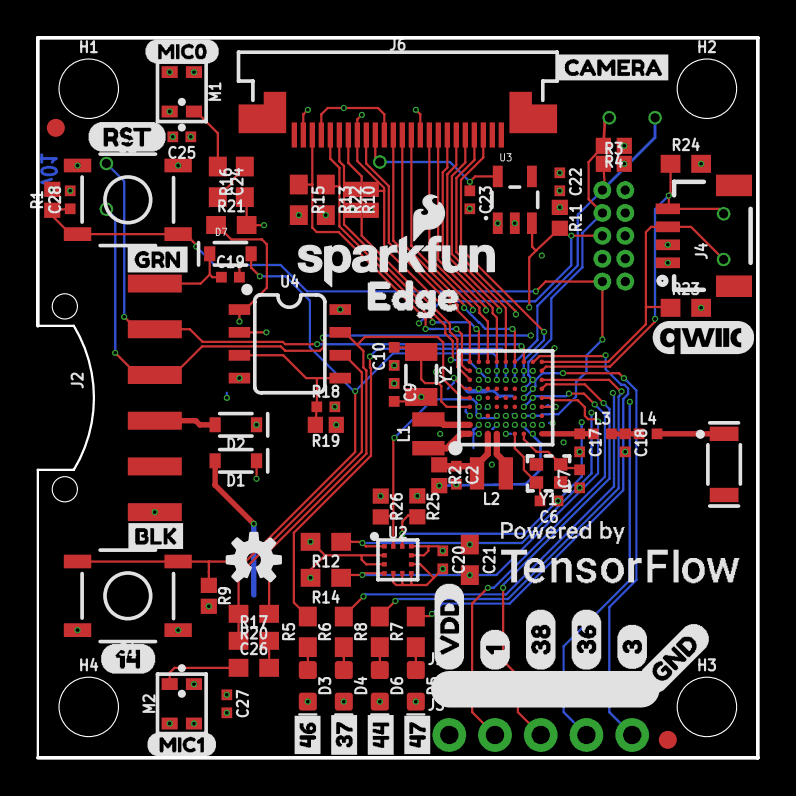
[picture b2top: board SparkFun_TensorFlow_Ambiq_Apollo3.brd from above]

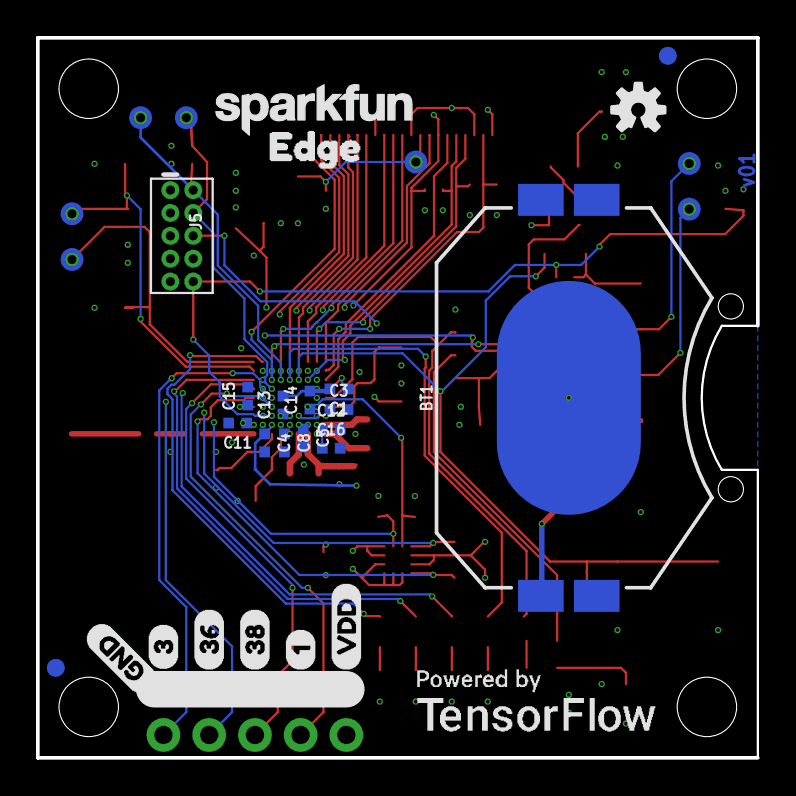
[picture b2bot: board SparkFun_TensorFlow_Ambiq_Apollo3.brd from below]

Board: 4 copper layers, 40.0 x 40.0 mm, 132 parts (32 on the bottom side), 74 nets.

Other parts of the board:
U$1: MIC00
U$2: BLK2
U$3, U$14: GND0
U$4, U$9: VDD1
U$5, U$8: 10
U$6, U$11: 383
U$7, U$12: 364
U$10, U$13: 31
U$15: 461
U$16: 372
U$17: 443
U$18: 470
U$19: QWIIC_COPYRIGHT_SMALL
U$20: CAMERA3
U$21, U$25: POWEREDBY_TF#JPG
U$22: MIC11
U$23, U$24: EDGE0
U$26: 1416
U$27: RST15
U$28: GRN1
U$29: SFE_LOGO_NAME_.1
U$30: OSHW-LOGO-S

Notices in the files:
parts and their libraries:
SparkFun-Aesthetics: Licensing: Creative Commons ShareAlike 4.0 International - https://creativecommons.org/licenses/by-sa/4.0
SparkFun-Aesthetics: Released under the Creative Commons Attribution Share-Alike 4.0 License
SparkFun-Aesthetics: https://creativecommons.org/licenses/by-sa/4.0
